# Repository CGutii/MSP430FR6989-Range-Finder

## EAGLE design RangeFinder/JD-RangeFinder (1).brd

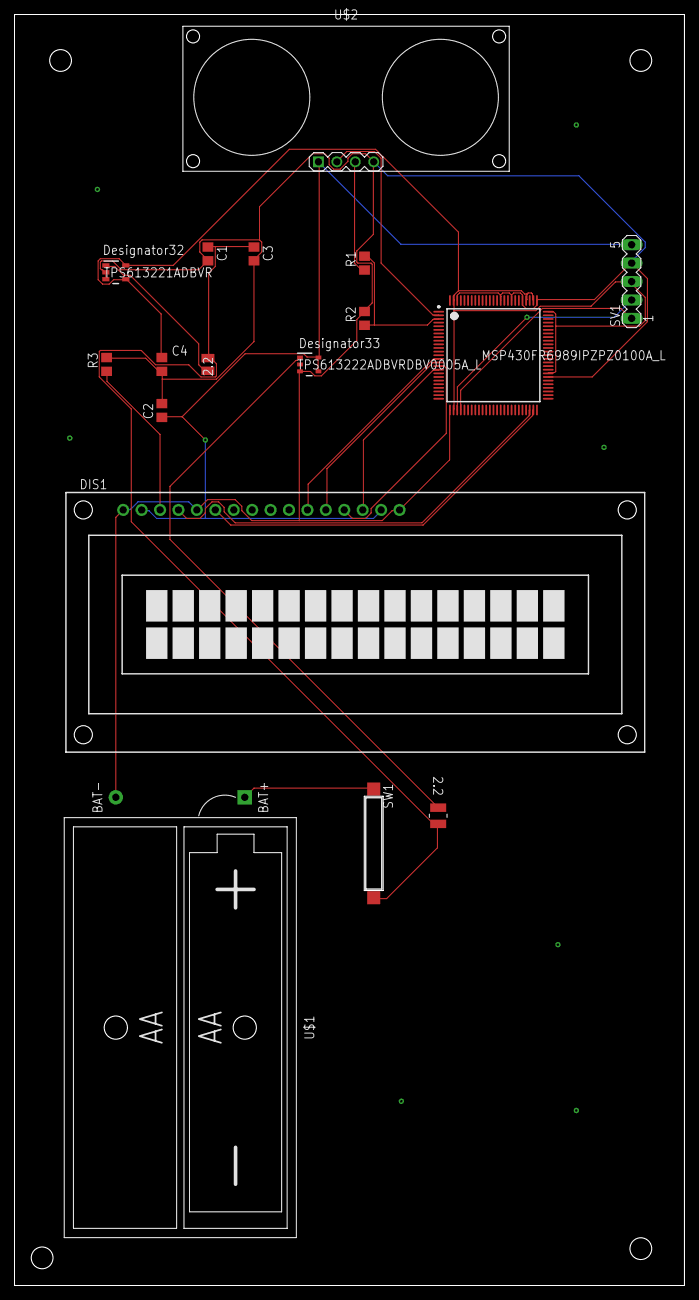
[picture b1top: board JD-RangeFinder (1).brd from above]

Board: 2 copper layers, 92.4 x 175.2 mm, 17 parts (0 on the bottom side), 19 nets.

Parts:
C1, C3: 4.7; C0805
C2, C4: 22; C0805
DIS1: TUXGR_16X2_R2
L1: 2.2; IND_LQM2HPN2R2MG0L_MUR
L2: 2.2; IND_1286AS-H-2R2M=P2_MUR
R1: 1k; R0805
R2: 2k; R0805
R3: 1K; R0805
SV1: MA05-1
SW1: CT10-XXXX-A2
U1: MSP430FR6989IPZPZ0100A_L; PZ0100A_L
U2: TPS613222ADBVRDBV0005A_L; DBV0005A_L
U3: TPS613221ADBVR; DBV0005A_N
U$1: BATTERY-HOLDER-2AA
U$2: ULTRASONIC-HC-SR04

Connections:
3.3V_OUTPUT: C4.1, SV1.3, U1.27, U1.58, U1.75, U1.77, U1.79, U1.99, U3.4, U3.5
5V_OUTPUT: C2.1, DIS1.2, DIS1.15, SV1.5, U2.4, U2.5, U$2.1
BAT_PLUS_OUTPUT: C1.1, C3.1, L1.2, L2.2, SW1.2
GND: C1.2, C2.2, C3.2, C4.2, DIS1.1, DIS1.5, DIS1.16, R2.2, R3.2, SV1.4, U1.26, U1.57, U1.76, U1.80, U1.83, U1.86, U1.98, U2.2, U2.3, U3.2, U3.3, U$1.BAT-, U$2.4
unnamed: R1.1, U$2.3
unnamed: L2.1, U3.1
unnamed: SW1.1, U$1.BAT+
unnamed: DIS1.3, R3.1
unnamed: L1.1, U2.1
P1.4: U1.2, U$2.2
P1.5: R1.2, R2.1, U1.3
P2.2: DIS1.6, U1.49
P2.3: DIS1.4, U1.48
P2.4: DIS1.11, U1.14
P2.5: DIS1.12, U1.15
P2.6: DIS1.13, U1.16
P2.7: DIS1.14, U1.17
RST: SV1.1, U1.29
TST: SV1.2, U1.28

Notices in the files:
parts and their libraries:
diy-modules: Released under the Creative Commons Attribution 4.0 International License: http://creativecommons.org/licenses/by/4.0
COPYRIGHT: Copyright (C) 2022 Ultra Librarian. All rights reserved.
